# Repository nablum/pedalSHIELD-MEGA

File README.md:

A programmable guitar effects shield for Arduino MEGA, featuring OLED display, true-bypass footswitch, and DSP-ready input/output stages. Based on pedalSHIELD MEGA by [ElectroSmash](https://www.electrosmash.com/pedalshield-mega)  

## 📦 What’s Included

- ✅ **KiCad project**: schematic & PCB layout files for the hardware shield
- ✅ **Arduino examples**: boost, fuzz, delay, and other DSP sketches
- ✅ **Bill of Materials**: CSV file with component list and Mouser links
- ✅ **Documentation**: assembly guide, schematic diagrams, signal flow

## 🛠️ Assembly & Programming

1. **Clone the repository**:

    ```bash
    git clone https://github.com/nablum/pedalSHIELD-MEGA.git
    cd pedalSHIELD-MEGA
    ```

2. **Build the PCB** with KiCad or order the board from a fab using the provided Gerbers.

3. **Solder the components** according to the [Assembly Guide](https://www.electrosmash.com/media/kunena/attachments/631/How-to-Build-pedalSHIELD-MEGA-V1.1.pdf).

4. **Upload an effect sketch** to your Arduino MEGA using Arduino IDE.
5. **Plug and play**:
    - Guitar IN → Input Jack
    - Output → Amp or Audio Interface
    - Power → USB or DC JACK.

## 🎛️ Example Effects

Each audio effect is implemented in a separate folder under [`firmware/effects/`](./firmware/effects/):

| Effect Name       | Description                                               |
|-------------------|-----------------------------------------------------------|
| BitCrusher        | Reduces resolution and sample rate for lo-fi textures     |
| Chorus            | Modulates pitch with delay to create a thickening effect  |
| ChorusOrVibrato   | Blendable chorus and vibrato with adjustable depth        |
| Clean             | Transparent clean boost (reference circuit)               |
| Distortion        | Hard-clipping distortion effect                           |
| Echo              | Simple digital delay with feedback loop                   |
| Fuzz              | Saturated high-gain fuzz effect                           |
| MultiEffects      | Combination of multiple effects in a single patch         |
| OctaveCrusher     | Bit reduction with added octave-up/down harmonics         |
| Octaver           | Mixes original with octave-down processed signal          |
| Reverb            | Simulates ambient reverb using delay-based algorithm      |
| Tremolo           | Volume modulation using a low-frequency oscillator        |
| Vibrato           | Pitch modulation effect for expressive shimmer            |

## ⚙️ Hardware Specs

- Compatible with **Arduino MEGA 2560**
- 128×64 I²C OLED display (SSD1306)
- True-bypass footswitch with relay
- Stereo audio jacks with analog preamp/output
- Powered via **12 V DC (center-negative)**

## ❓ Troubleshooting

- **OLED not lighting up** → Double-check I²C wiring and 4.7k pull-up resistors.
- **No audio output** → Ensure signal chain is complete and shield is powered.
- **Arduino upload fails** → Check USB port, board selection, and serial permissions.

## 📚 Resources

- 🔬 [pedalSHIELD-MEGA Documentation – ElectroSmash](https://www.electrosmash.com/pedalshield-mega)  
  Official guide, schematics, theory of operation, and signal path details.

- 🧰 [Assembly Guide – PDF](https://www.electrosmash.com/media/kunena/attachments/631/How-to-Build-pedalSHIELD-MEGA-V1.1.pdf)  
  Step-by-step instructions with images for building the pedalSHIELD‑MEGA hardware.

- 📦 [u8glib – OLED Display Library](https://github.com/olikraus/u8glib)  
  Arduino graphics library used to drive the OLED screen (SSD1306, I²C).

- 💻 [Arduino IDE Downloads](https://www.arduino.cc/en/software/)  
  Install the Arduino IDE to compile and upload code to the MEGA 2560.

## 🤝 Contributing

Contributions are welcome! You can:

- Submit new audio effects or improvements to existing sketches.
- Suggest hardware upgrades (e.g. better op-amps, analog filtering).
- Improve documentation or add new troubleshooting tips.

Please open a pull request against the `main` branch and follow the coding style of existing files.

## 📄 License

- **Hardware (PCB files, schematics, BOM)**:  
  Licensed under [Creative Commons Attribution-NonCommercial 3.0 (CC BY-NC 3.0)](https://creativecommons.org/licenses/by-nc/3.0/)

- **Software (Arduino code, examples)**:  
  Licensed under the [MIT License](LICENSE)

## 📬 Contact

Created by [@nablum](https://github.com/nablum).  
For questions or collaboration ideas, feel free to open an issue or reach out directly.

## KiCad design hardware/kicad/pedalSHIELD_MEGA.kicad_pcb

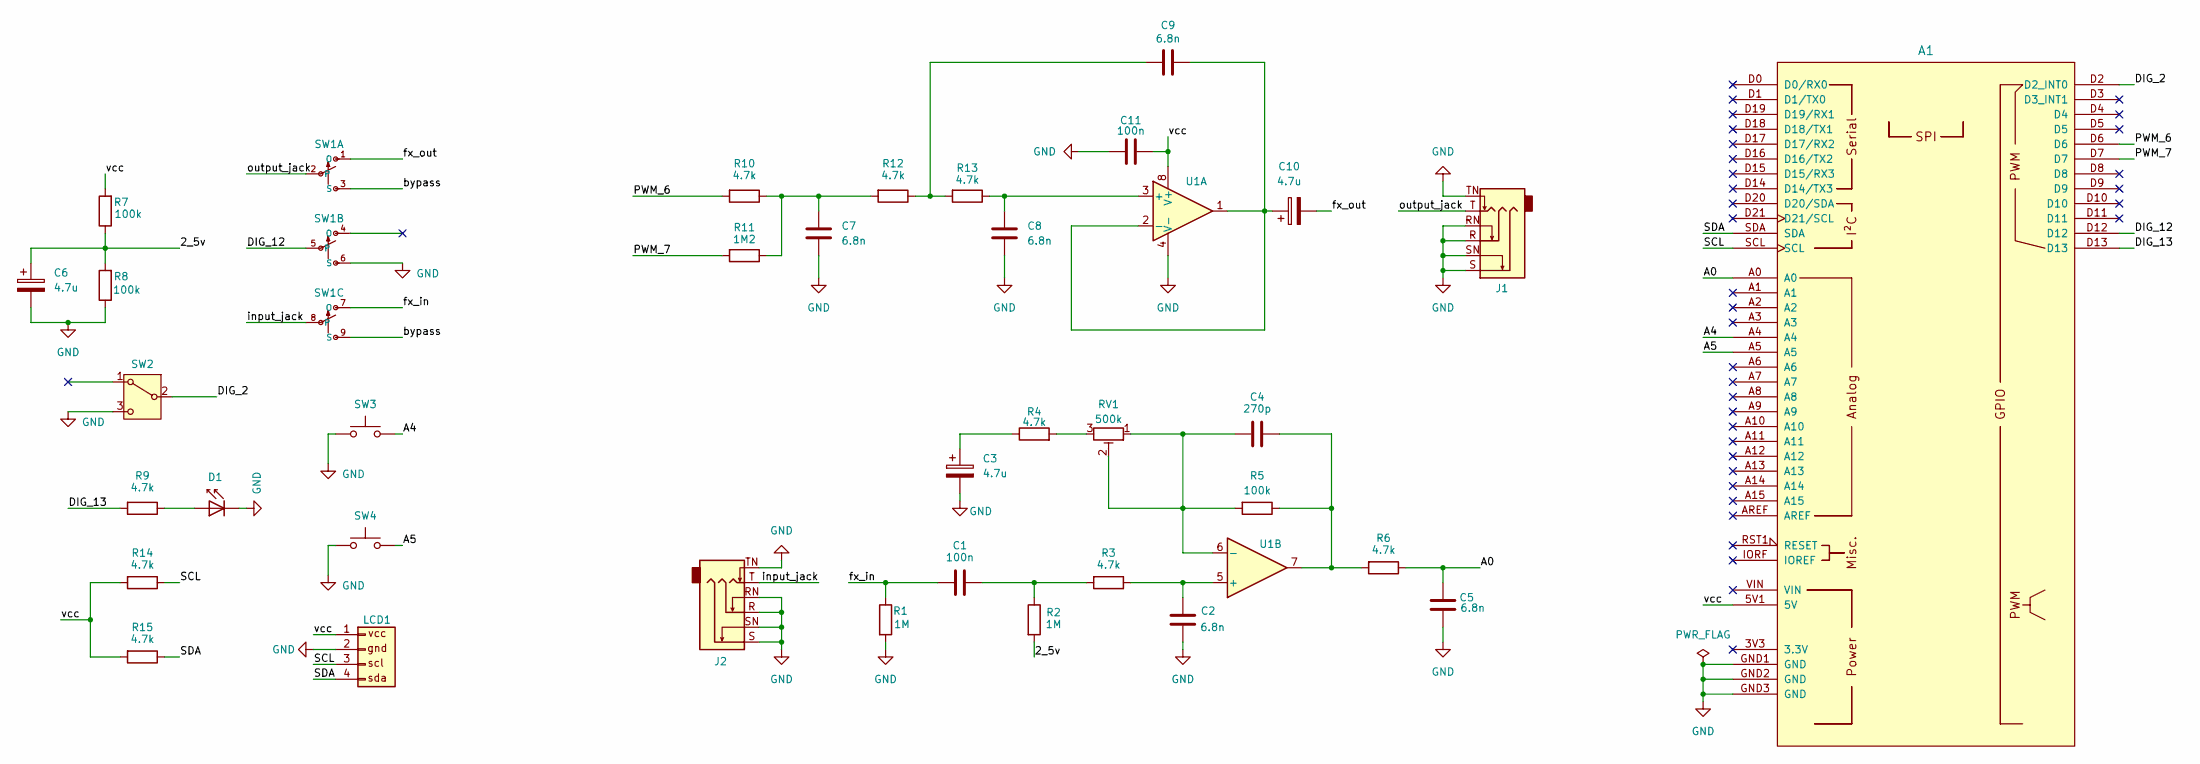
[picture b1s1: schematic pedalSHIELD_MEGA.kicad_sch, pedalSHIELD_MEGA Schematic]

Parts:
A1: Arduino_Mega2560_R3_Shield_pedalSHIELD_MEGA; Mouser 782-A000067
C1, C11: 100n; C_Rect_L7.0mm_W2.5mm_P5.00mm; Mouser SR211C
C2, C5, C7, C8, C9: 6.8n; C_Rect_L7.0mm_W2.5mm_P5.00mm; Mouser SR211C
C3, C6, C10: 4.7u; CP_Radial_D4.0mm_P1.50mm; Mouser ECE-A1EKA4R7
C4: 270p; C_Rect_L7.0mm_W2.5mm_P5.00mm; Mouser SR211C
D1: LED_D3.0mm; Mouser 696-SSL-LX3044USBC
J1, J2: Jack_6.35mm_Neutrik_NMJ6HCD2_Horizontal; Mouser NMJ6HCD2
LCD1: LCD_OLED_SH1106
R1, R2: 1M; R_Axial_DIN0207_L6.3mm_D2.5mm_P7.62mm_Horizontal; Mouser MFR-25FRF52
R3, R4, R6, R9, R10, R12, R13, R14, R15: 4.7k; R_Axial_DIN0207_L6.3mm_D2.5mm_P7.62mm_Horizontal; Mouser MFR-25FRF52
R5, R7, R8: 100k; R_Axial_DIN0207_L6.3mm_D2.5mm_P7.62mm_Horizontal; Mouser MFR-25FRF52
R11: 1M2; R_Axial_DIN0207_L6.3mm_D2.5mm_P7.62mm_Horizontal; Mouser MFR-25FRF52
RV1: 500k; Potentiometer_Piher_PT-10-H01_Horizontal; Mouser PT10LH01-504A2020
SW1: SF17020F030221RL015; Manufacturer_Part_Number SF17020F-0302-21R-L-015; Mouser 107-SF17020F-32-21RL
SW2: SW_SPDT_ 100SP1T1B1M1QEH; Mouser 100SP1T1B1M1QEH
SW3, SW4: SW_PUSH_104-0013-EVX; Mouser 104-0013-EVX
U1: DIP-8_W7.62mm_Socket_LongPads; Mouser 595-TL972IP

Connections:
/2_5v: C6.1, R2.2, R7.1, R8.2
/A0: A1.A0, C5.1, R6.1
/A4: A1.A4, SW3.2
/A5: A1.A5, SW4.2
/DIG_2: A1.D2 (D2_INT0), SW2.2 (B)
/DIG_12: A1.D12, SW1.5
/DIG_13: A1.D13, R9.2
/PWM_6: A1.D6, R10.2
/PWM_7: A1.D7, R11.2
/SCL: A1.SCL, LCD1.3, R14.1
/SDA: A1.SDA, LCD1.4, R15.1
/bypass: SW1.3 (S), SW1.9 (S)
/fx_in: C1.1, R1.1, SW1.7 (O)
/fx_out: C10.2, SW1.1 (O)
/input_jack: J2.T, SW1.8
/output_jack: J1.T, SW1.2
/vcc: A1.5V1 (5V), C11.2, LCD1.1, R7.2, R14.2, R15.2, U1.8 (V+)
GND: A1.GND1 (GND), A1.GND2 (GND), A1.GND3 (GND), C2.2, C3.2, C5.2, C6.2, C7.2, C8.2, C11.1, D1.1 (K), J1.R, J1.RN, J1.S, J1.SN, J1.TN, J2.R, J2.RN, J2.S, J2.SN, J2.TN, LCD1.2, R1.2, R8.1, SW1.6 (S), SW2.3 (C), SW3.1, SW4.1, U1.4 (V-)
unnamed: C1.2, R2.1, R3.2
unnamed: C3.1, R4.1
unnamed: C4.2, R5.1, R6.2, U1.7
unnamed: C7.1, R10.1, R11.1, R12.2
unnamed: C9.1, R12.1, R13.2
unnamed: D1.2 (A), R9.1
unnamed: R4.2, RV1.3
unnamed: C8.1, R13.1, U1.3 (+)
unnamed: C9.2, C10.1, U1.1, U1.2 (-)
unnamed: C2.1, R3.1, U1.5 (+)
unnamed: C4.1, R5.2, RV1.1, RV1.2, U1.6 (-)

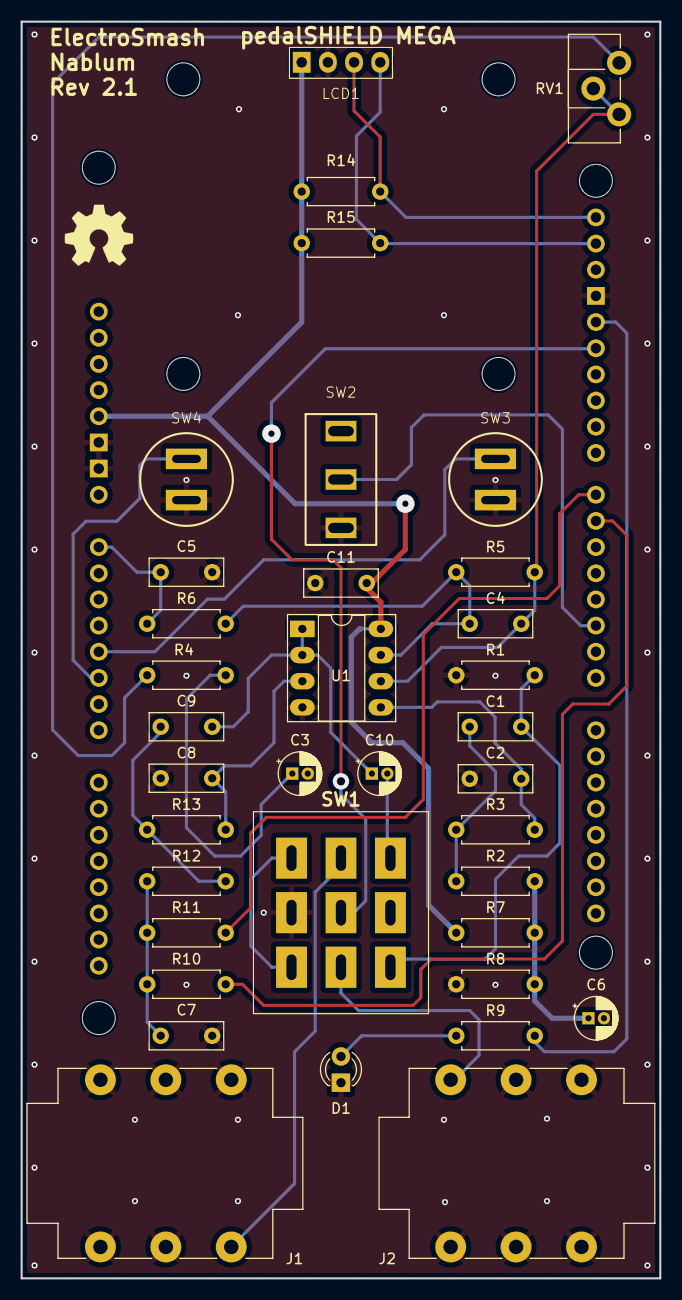
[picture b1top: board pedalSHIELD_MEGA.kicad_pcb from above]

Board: 2 copper layers, 62.0 x 122.0 mm, 37 parts (0 on the bottom side), 29 nets.

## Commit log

2024-09-20 .gitignore update
2024-09-20 kicad project update
2024-09-20 README.md update
2024-09-20 code update
2024-09-21 renamed folder
2025-03-25 update .gitignore
    ignore vscode settings
2025-03-25 display function
2025-03-25 audio effects library update
2025-03-25 license update
2025-03-25 .gitignore update
    freecad files
2025-03-25 freecad project update
2025-03-27 move from freecad to openscad
2025-04-09 library update
2025-04-09 rev 2.1
2025-04-09 3D model update
2025-04-09 pedal assembly
2025-04-10 case base design
2025-04-10 case left side design
2025-04-10 case bottom/right side design
2025-04-12 top panel design
2025-04-14 brackets
2025-04-14 add .gitmodules
2025-04-14 board mounts
2025-04-14 export .stl
2025-04-15 svg export
2025-04-18 octaver added to multi-effects
2025-04-18 chorus and vibrato added to multi-effects
2025-04-18 header update

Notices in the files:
README.md:
License: CC BY-NC
License: MIT
